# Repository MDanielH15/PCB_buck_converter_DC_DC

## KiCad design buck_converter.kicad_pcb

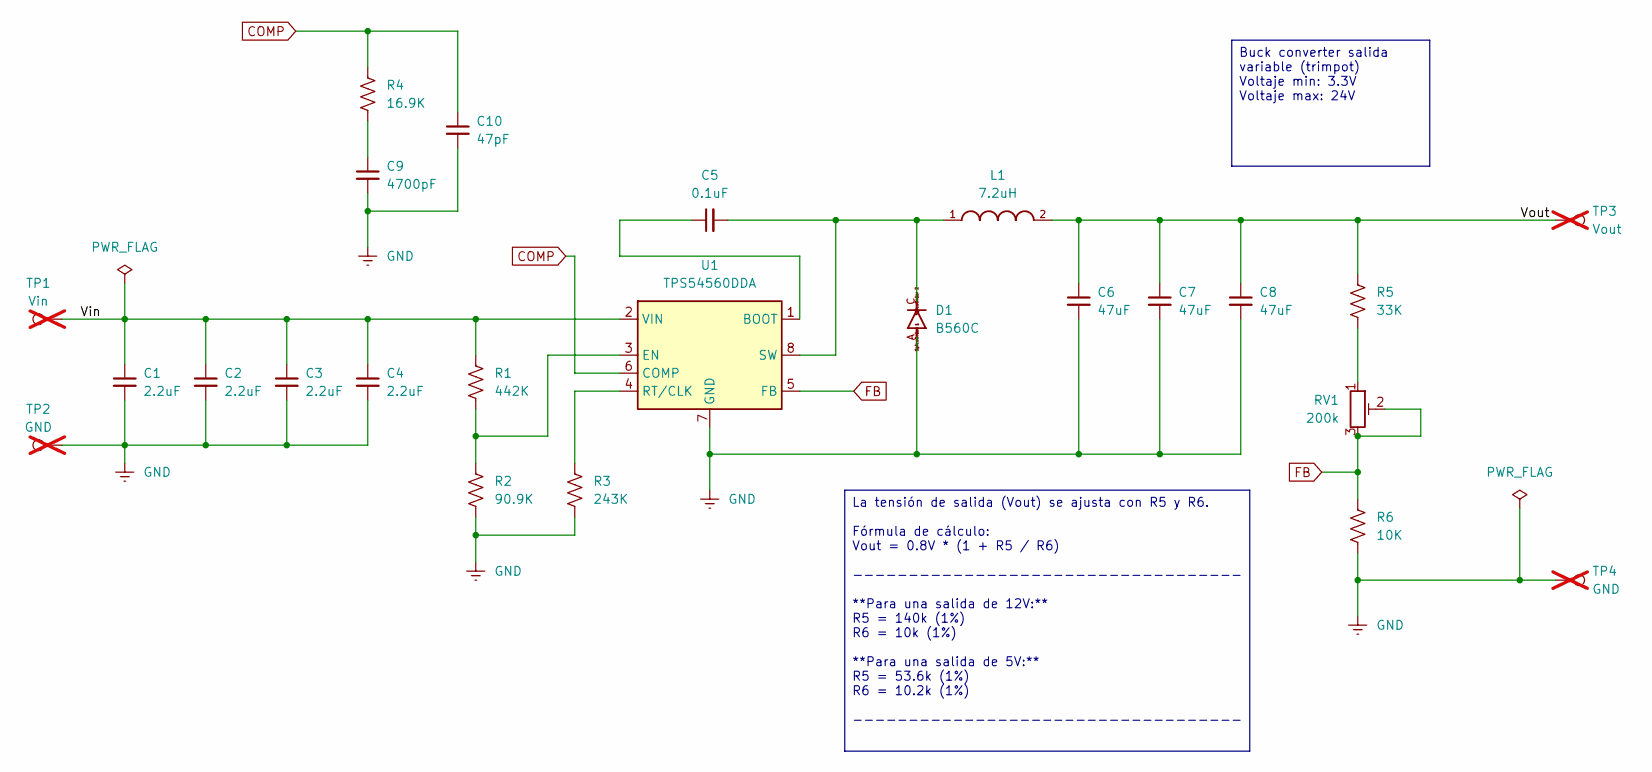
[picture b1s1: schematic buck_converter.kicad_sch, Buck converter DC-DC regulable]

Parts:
C1, C2, C3: 2.2uF; C_1210_3225Metric
C4: 2.2uF; C_0805_2012Metric
C5: 0.1uF; C_0805_2012Metric
C6, C7, C8: 47uF; C_1210_3225Metric
C9: 4700pF; C_0805_2012Metric
C10: 47pF; C_0805_2012Metric
D1: B560C; SMC
L1: 7.2uH; WE-PDF_1064
R1: 442K; R_0805_2012Metric
R2: 90.9K; R_0805_2012Metric
R3: 243K; R_0805_2012Metric
R4: 16.9K; R_0805_2012Metric
R5: 33K; R_0805_2012Metric
R6: 10K; R_0805_2012Metric
RV1: 200k; Potentiometer_Bourns_3214W_Vertical
TP1: Vin; TestPoint_THTPad_2.0x2.0mm_Drill1.0mm; not fitted
TP2, TP4: GND; TestPoint_THTPad_2.0x2.0mm_Drill1.0mm; not fitted
TP3: Vout; TestPoint_THTPad_2.0x2.0mm_Drill1.0mm; not fitted
U1: TPS54560DDA; Texas_R-PDSO-G8_EP2.95x4.9mm_Mask2.4x3.1mm_ThermalVias

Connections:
/Vin: C1.1, C2.1, C3.1, C4.1, R1.1, TP1.1, U1.2 (VIN)
/Vout: C6.1, C7.1, C8.1, L1.2, R5.1, TP3.1
COMP: C10.1, R4.1, U1.6 (COMP)
FB: R6.1, RV1.2, RV1.3, U1.5 (FB)
GND: C1.2, C2.2, C3.2, C4.2, C6.2, C7.2, C8.2, C9.2, C10.2, D1.A, R2.2, R3.2, R6.2, TP2.1, TP4.1, U1.7 (GND), U1.9 (GND)
unnamed: C9.1, R4.2
unnamed: R5.2, RV1.1
unnamed: C5.1, U1.1 (BOOT)
unnamed: R1.2, R2.1, U1.3 (EN)
unnamed: R3.1, U1.4 (RT/CLK)
unnamed: C5.2, D1.C, L1.1, U1.8 (SW)

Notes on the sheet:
La tensión de salida (Vout) se ajusta con R5 y R6. Fórmula de cálculo: Vout = 0.8V * (1 + R5 / R6) ----------------------------------- **Para una salida de 12V:** R5 = 140k (1%) R6 = 10k (1%) **Para una salida de 5V:** R5 = 53.6k (1%) R6 = 10.2k (1%) -----------------------------------
Buck converter salida variable (trimpot) Voltaje min: 3.3V Voltaje max: 24V

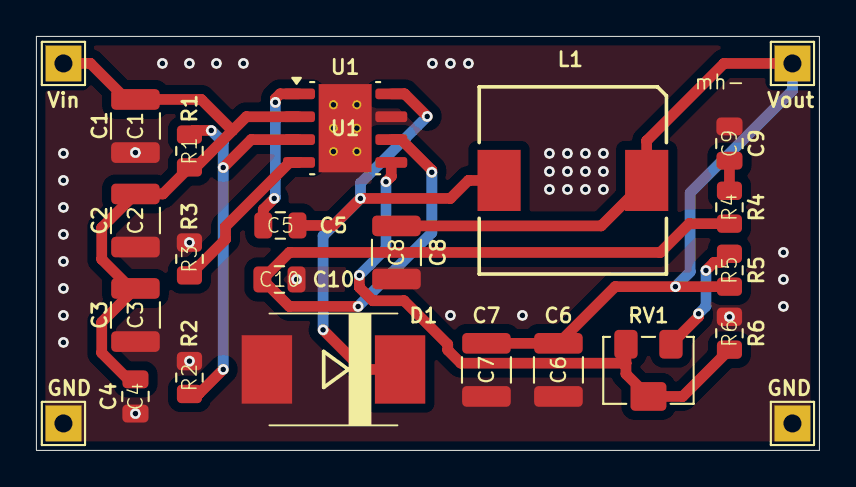
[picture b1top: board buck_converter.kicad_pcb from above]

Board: 2 copper layers, 43.5 x 23.0 mm, 24 parts (0 on the bottom side), 11 nets.

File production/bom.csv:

Designator,Footprint,Quantity,Value,LCSC Part #
"C1, C2, C3",1210,3,2.2uF,
C10,0805,1,47pF,
C4,0805,1,2.2uF,
C5,0805,1,0.1uF,
"C6, C7, C8",1210,3,47uF,
C9,0805,1,4700pF,
D1,SMC,1,B560C,
L1,WE-PDF_1064,1,7.2uH,
R1,0805,1,442K,
R2,0805,1,90.9K,
R3,0805,1,243K,
R4,0805,1,16.9K,
R5,0805,1,33K,
R6,0805,1,10K,
RV1,Potentiometer_Bourns_3214W_Vertical,1,250k,
TP1,TestPoint_THTPad_2.0x2.0mm_Drill1.0mm,1,Vin,
"TP2, TP4",TestPoint_THTPad_2.0x2.0mm_Drill1.0mm,2,GND,
TP3,TestPoint_THTPad_2.0x2.0mm_Drill1.0mm,1,Vout,
U1,Texas_R-PDSO-G8_EP2.95x4.9mm_Mask2.4x3.1mm_ThermalVias,1,TPS54560DDA,

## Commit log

2025-10-22 "version 1"
2025-10-23 "Versión 2"
